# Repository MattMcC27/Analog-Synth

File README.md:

# Analog-Synth

My personal Analog Voltage Controlled Oscilator, wave shapers, and output stage

## Behavior

## Wave Shape Photos at decreasing frequency

## Audio Demo

https://github.com/user-attachments/assets/6dd11a05-b424-4769-ac00-267ce8dbd173

https://github.com/user-attachments/assets/6da5949c-7cdd-406b-b645-f12ac689b7d8

https://github.com/user-attachments/assets/ecf994ba-5ef1-4e04-878b-3f7e2e97198b

https://github.com/user-attachments/assets/66918d8a-2ba2-4e4a-80ee-363ddde3f1d2

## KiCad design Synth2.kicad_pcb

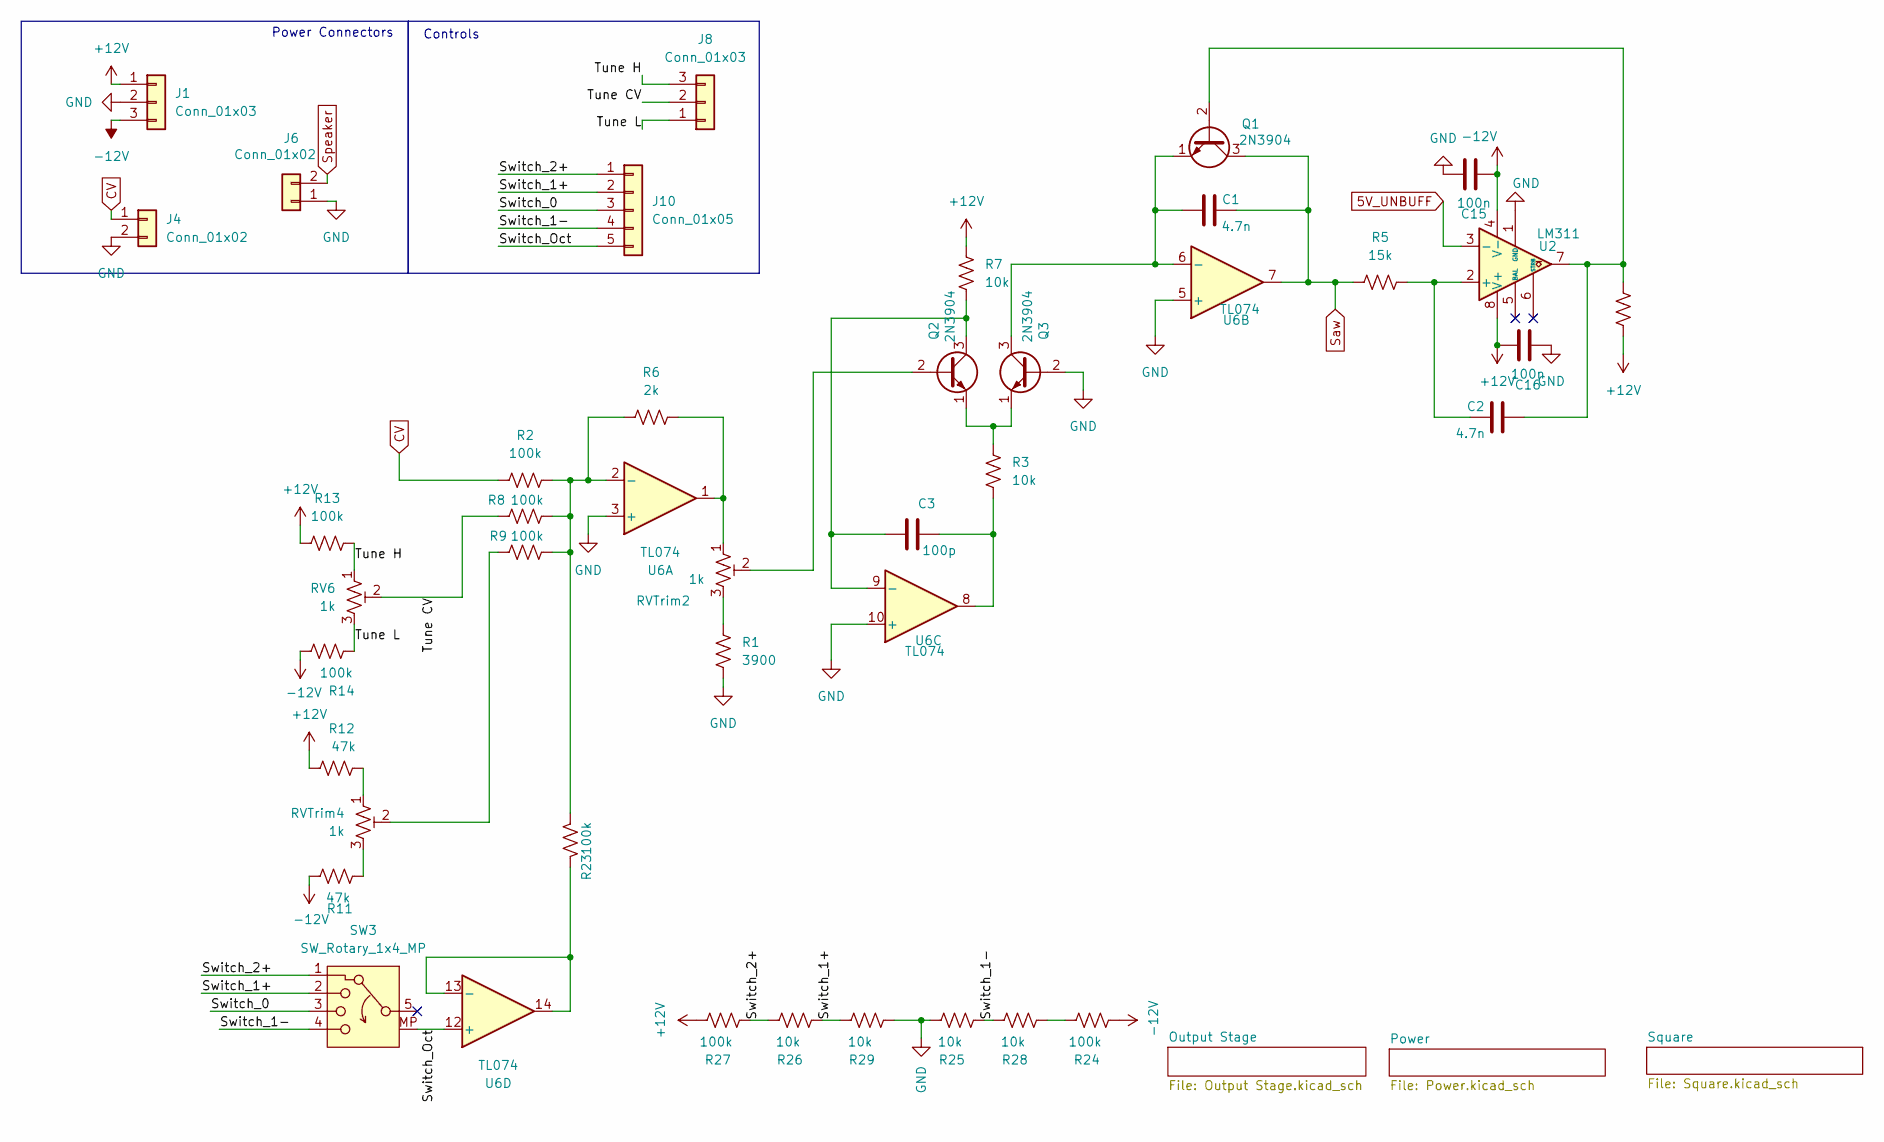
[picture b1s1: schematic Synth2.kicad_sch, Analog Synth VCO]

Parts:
C1, C2: 4.7n; C_Disc_D5.0mm_W2.5mm_P5.00mm
C3: 100p; C_Disc_D5.0mm_W2.5mm_P5.00mm
C15, C16: 100n; C_Disc_D5.0mm_W2.5mm_P5.00mm
J1, J8: Conn_01x03; JST_XH_B3B-XH-A_1x03_P2.50mm_Vertical
J4, J6: Conn_01x02; JST_XH_B2B-XH-A_1x02_P2.50mm_Vertical
J10: Conn_01x05; JST_XH_B5B-XH-A_1x05_P2.50mm_Vertical
Q1, Q2, Q3: 2N3904; MYNPN
R1: 3900; R_Axial_DIN0207_L6.3mm_D2.5mm_P7.62mm_Horizontal
R2, R8, R9, R13, R14, R23, R24, R27: 100k; R_Axial_DIN0207_L6.3mm_D2.5mm_P7.62mm_Horizontal
R3, R4, R7, R25, R26, R28, R29: 10k; R_Axial_DIN0207_L6.3mm_D2.5mm_P7.62mm_Horizontal
R5: 15k; R_Axial_DIN0207_L6.3mm_D2.5mm_P7.62mm_Horizontal
R6: 2k; R_Axial_DIN0207_L6.3mm_D2.5mm_P7.62mm_Horizontal
R11, R12: 47k; R_Axial_DIN0207_L6.3mm_D2.5mm_P7.62mm_Horizontal
RV6: 1k
RVTrim2, RVTrim4: 1k; Potentiometer_Bourns_3296W_Vertical
SW3: SW_Rotary_1x4_MP
U2: LM311; MY311
U6: TL074; MYTL074

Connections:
5V_UNBUFF: U2.3 (-); also elsewhere on the board
+12V: C16.2, J1.1, R4.1, R7.1, R12.2, R13.2, R27.1, U2.8 (V+); also elsewhere on the board
-12V: C15.1, J1.3, R11.2, R14.2, R24.2, U2.4 (V-); also elsewhere on the board
/Switch_0: J10.3, SW3.3
/Switch_1+: J10.2, R26.2, R29.1, SW3.2
/Switch_1-: J10.4, R25.2, R28.1, SW3.4
/Switch_2+: J10.1, R26.1, R27.2, SW3.1
/Switch_Oct: J10.5, SW3.MP, U6.12 (+)
/Tune CV: J8.2, R8.1, RV6.2
/Tune H: J8.3, R13.1, RV6.1
/Tune L: J8.1, R14.1, RV6.3
CV: J4.1, R2.1
GND: C15.2, C16.1, J1.2, J4.2, J6.1, Q3.2 (B), R1.2, R25.1, R29.2, U2.1 (GND), U6.3 (+), U6.5 (+), U6.10 (+); also elsewhere on the board
unnamed: C3.2, R3.2, U6.8
unnamed: C2.1, Q1.2 (B), R4.2, U2.7
unnamed: C1.1, Q1.1 (E), Q3.3 (C), U6.6 (-)
unnamed: Q2.2 (B), RVTrim2.2
unnamed: C3.1, Q2.3 (C), R7.2, U6.9 (-)
unnamed: Q2.1 (E), Q3.1 (E), R3.1
unnamed: R1.1, RVTrim2.3
unnamed: R6.2, RVTrim2.1, U6.1
unnamed: R9.1, RVTrim4.2
unnamed: R11.1, RVTrim4.3
unnamed: R12.1, RVTrim4.1
unnamed: R24.1, R28.2
unnamed: C2.2, R5.1, U2.2 (+)
unnamed: R2.2, R6.1, R8.2, R9.2, R23.2, U6.2 (-)
unnamed: R23.1, U6.13 (-), U6.14
Saw: C1.2, Q1.3 (C), R5.2, U6.7; also elsewhere on the board
Speaker: J6.2; also elsewhere on the board

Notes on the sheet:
Power Connectors
Controls

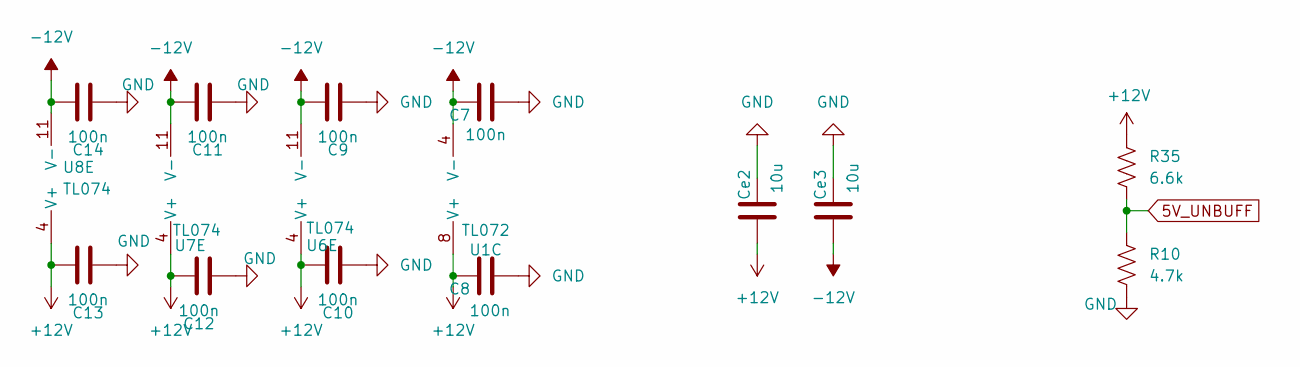
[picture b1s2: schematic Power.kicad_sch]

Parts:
C7, C8, C9, C10, C11, C12, C13, C14: 100n; C_Disc_D5.0mm_W2.5mm_P5.00mm
Ce2, Ce3: 10u; CP_Radial_D5.0mm_P2.50mm
R10: 4.7k; R_Axial_DIN0207_L6.3mm_D2.5mm_P7.62mm_Horizontal
R35: 6.6k; R_Axial_DIN0207_L6.3mm_D2.5mm_P7.62mm_Horizontal
U1: TL072; MYTL072
U6, U7, U8: TL074; MYTL074

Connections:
5V_UNBUFF: R10.2, R35.1; also elsewhere on the board
+12V: C8.2, C10.2, C12.1, C13.2, Ce2.1, R35.2, U1.8 (V+), U6.4 (V+), U7.4 (V+), U8.4 (V+); also elsewhere on the board
-12V: C7.2, C9.2, C11.2, C14.2, Ce3.1, U1.4 (V-), U6.11 (V-), U7.11 (V-), U8.11 (V-); also elsewhere on the board
GND: C7.1, C8.1, C9.1, C10.1, C11.1, C12.2, C13.1, C14.1, Ce2.2, Ce3.2, R10.1; also elsewhere on the board

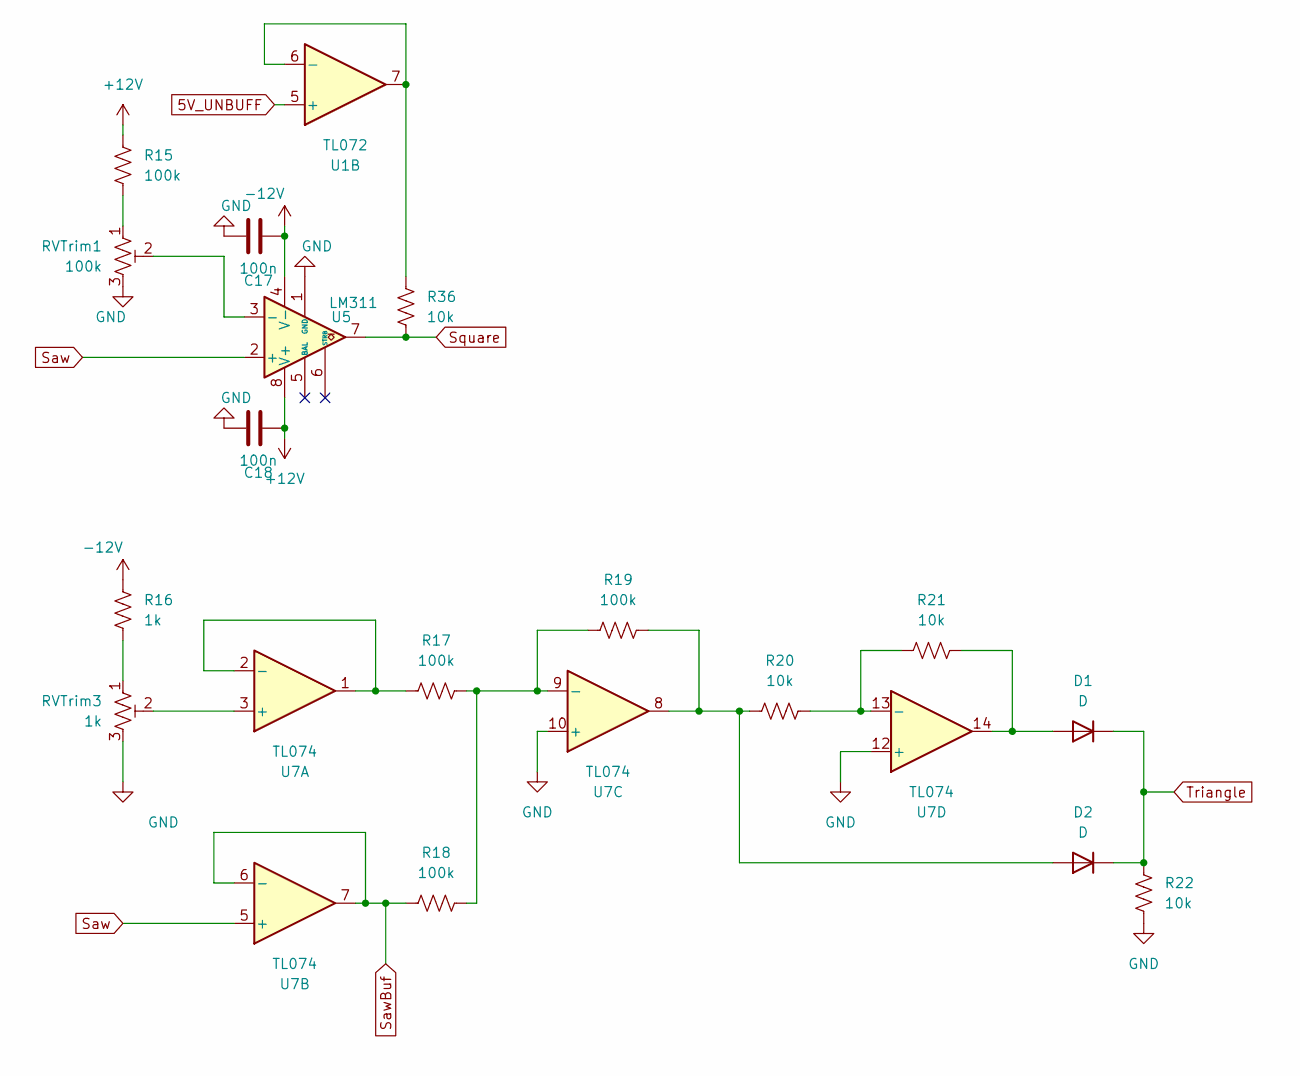
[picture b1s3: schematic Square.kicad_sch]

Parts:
C17, C18: 100n; C_Disc_D5.0mm_W2.5mm_P5.00mm
D1, D2: D; MYDIODE2
R15, R17, R18, R19: 100k; R_Axial_DIN0207_L6.3mm_D2.5mm_P7.62mm_Horizontal
R16: 1k; R_Axial_DIN0207_L6.3mm_D2.5mm_P7.62mm_Horizontal
R20, R21, R22, R36: 10k; R_Axial_DIN0207_L6.3mm_D2.5mm_P7.62mm_Horizontal
RVTrim1: 100k; Potentiometer_Bourns_3296W_Vertical
RVTrim3: 1k; Potentiometer_Bourns_3296W_Vertical
U1: TL072; MYTL072
U5: LM311; MY311
U7: TL074; MYTL074

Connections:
5V_UNBUFF: U1.5 (+); also elsewhere on the board
+12V: C18.1, R15.2, U5.8 (V+); also elsewhere on the board
-12V: C17.1, R16.2, U5.4 (V-); also elsewhere on the board
GND: C17.2, C18.2, R22.2, RVTrim1.3, RVTrim3.3, U5.1 (GND), U7.10 (+), U7.12 (+); also elsewhere on the board
unnamed: D1.2 (A), R21.1, U7.14
unnamed: D2.2 (A), R19.1, R20.2, U7.8
unnamed: R15.1, RVTrim1.1
unnamed: R16.1, RVTrim3.1
unnamed: R36.2, U1.6 (-), U1.7
unnamed: RVTrim1.2, U5.3 (-)
unnamed: RVTrim3.2, U7.3 (+)
unnamed: R17.2, U7.1, U7.2 (-)
unnamed: R17.1, R18.1, R19.2, U7.9 (-)
unnamed: R20.1, R21.2, U7.13 (-)
Saw: U5.2 (+), U7.5 (+); also elsewhere on the board
SawBuf: R18.2, U7.6 (-), U7.7; also elsewhere on the board
Square: R36.1, U5.7; also elsewhere on the board
Triangle: D1.1 (K), D2.1 (K), R22.1; also elsewhere on the board

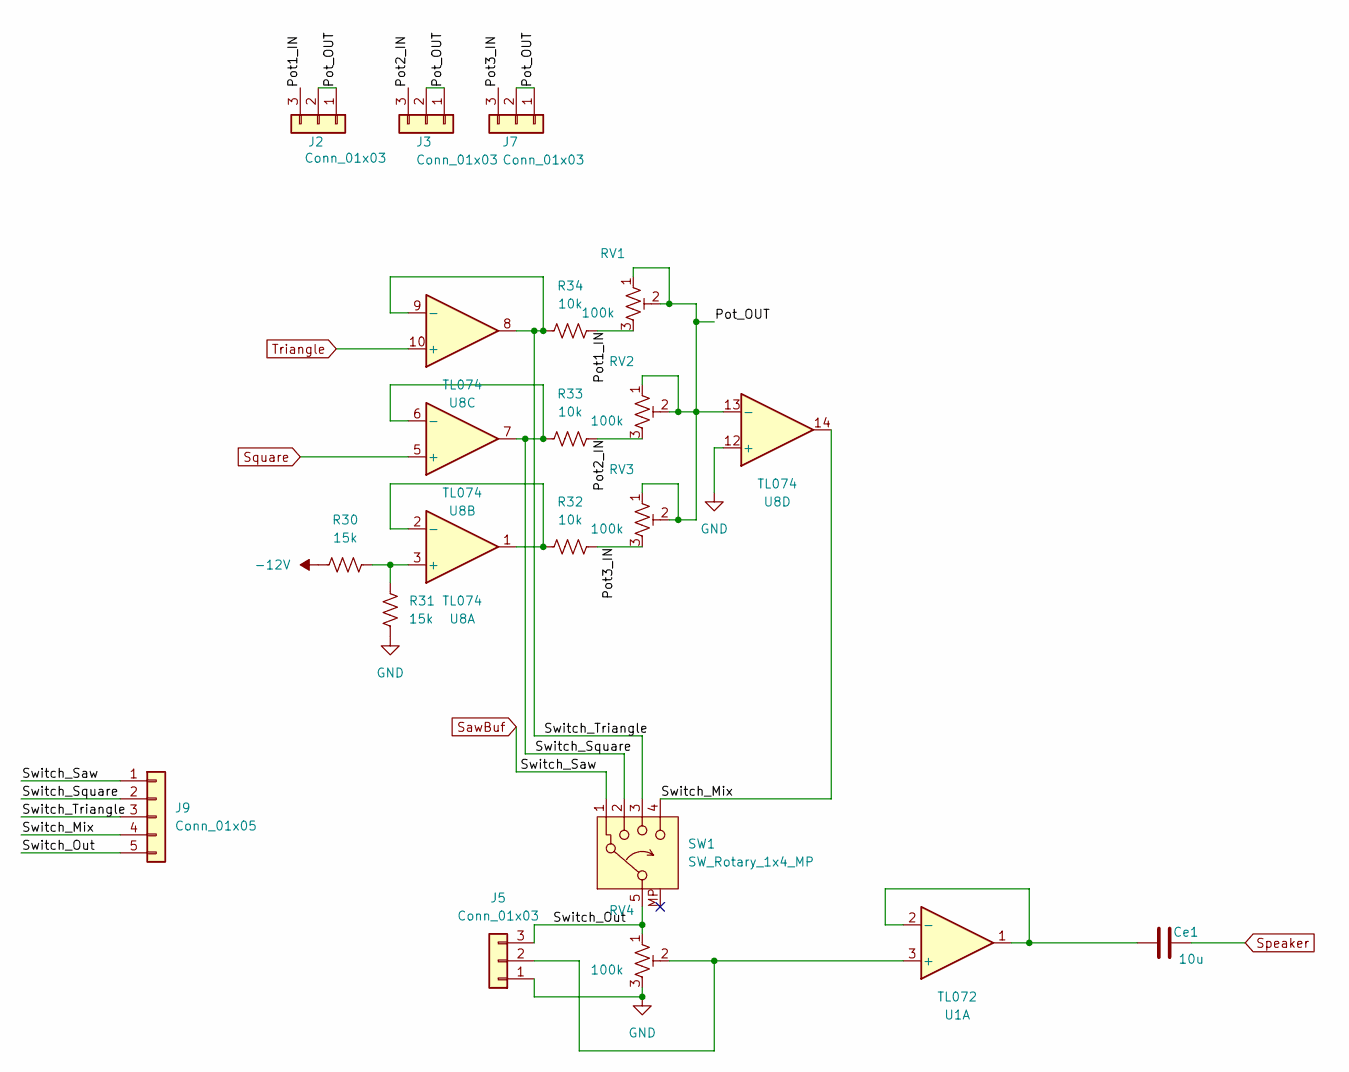
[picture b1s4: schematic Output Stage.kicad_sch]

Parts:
Ce1: 10u; CP_Radial_D5.0mm_P2.50mm
J2, J3, J5, J7: Conn_01x03; JST_XH_B3B-XH-A_1x03_P2.50mm_Vertical
J9: Conn_01x05; JST_XH_B5B-XH-A_1x05_P2.50mm_Vertical
R30, R31: 15k; R_Axial_DIN0207_L6.3mm_D2.5mm_P7.62mm_Horizontal
R32, R33, R34: 10k; R_Axial_DIN0207_L6.3mm_D2.5mm_P7.62mm_Horizontal
RV1, RV2, RV3, RV4: 100k
SW1: SW_Rotary_1x4_MP
U1: TL072; MYTL072
U8: TL074; MYTL074

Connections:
-12V: R30.2; also elsewhere on the board
/Output Stage/Pot1_IN: J2.3, R34.1, RV1.3
/Output Stage/Pot2_IN: J3.3, R33.1, RV2.3
/Output Stage/Pot3_IN: J7.3, R32.1, RV3.3
/Output Stage/Pot_OUT: J2.1, J2.2, J3.1, J3.2, J7.1, J7.2, RV1.1, RV1.2, RV2.1, RV2.2, RV3.1, RV3.2, U8.13 (-)
/Output Stage/Switch_Mix: J9.4, SW1.4, U8.14
/Output Stage/Switch_Out: J5.3, J9.5, RV4.1, SW1.5
/Output Stage/Switch_Square: J9.2, R33.2, SW1.2, U8.6 (-), U8.7
/Output Stage/Switch_Triangle: J9.3, R34.2, SW1.3, U8.8, U8.9 (-)
GND: J5.1, R31.1, RV4.3, U8.12 (+); also elsewhere on the board
unnamed: J5.2, RV4.2, U1.3 (+)
unnamed: Ce1.1, U1.1, U1.2 (-)
unnamed: R30.1, R31.2, U8.3 (+)
unnamed: R32.2, U8.1, U8.2 (-)
SawBuf: J9.1, SW1.1; also elsewhere on the board
Speaker: Ce1.2; also elsewhere on the board
Square: U8.5 (+); also elsewhere on the board
Triangle: U8.10 (+); also elsewhere on the board

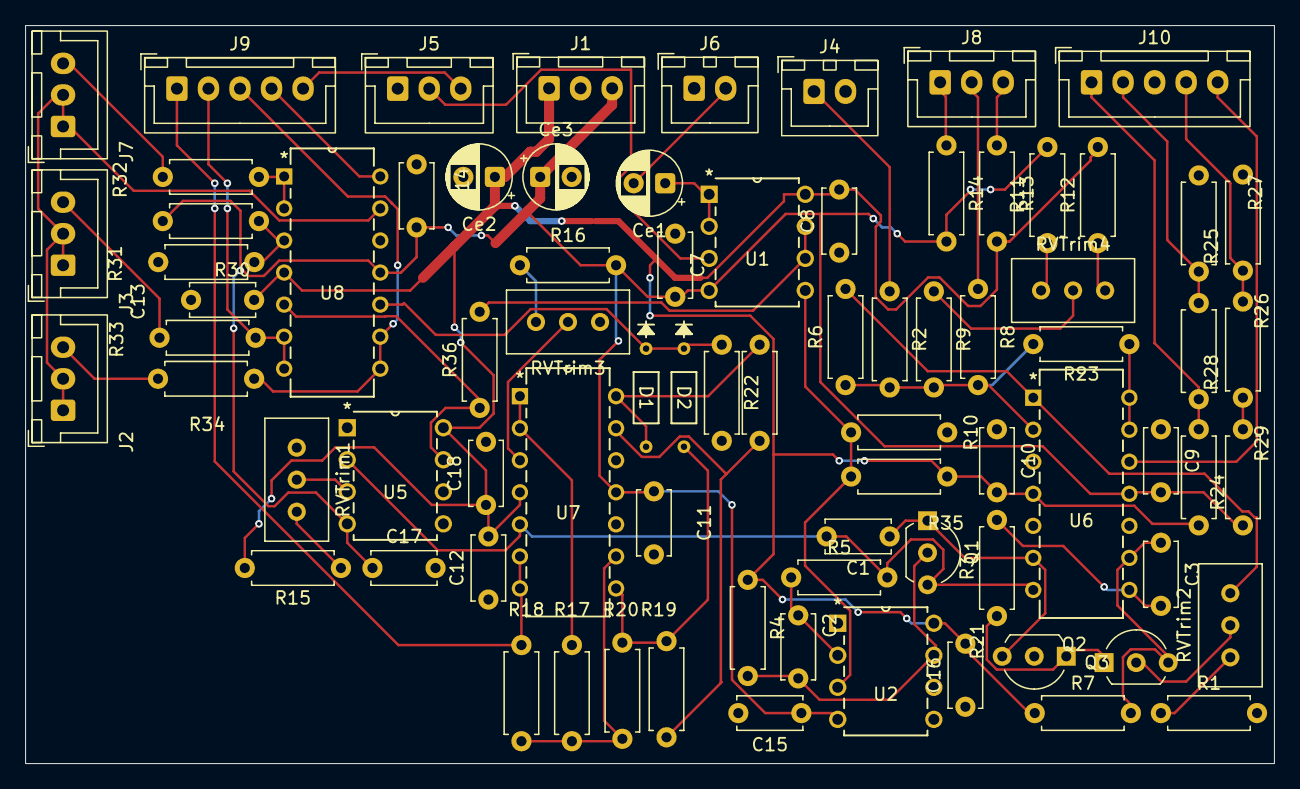
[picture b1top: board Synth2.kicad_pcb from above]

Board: 2 copper layers, 99.0 x 58.5 mm, 79 parts (0 on the bottom side), 54 nets.
